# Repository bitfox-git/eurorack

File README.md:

Bitfox Eurorack Modules
=======================

Code License: MIT License

Hardware License: CC-BY-SA 3.0

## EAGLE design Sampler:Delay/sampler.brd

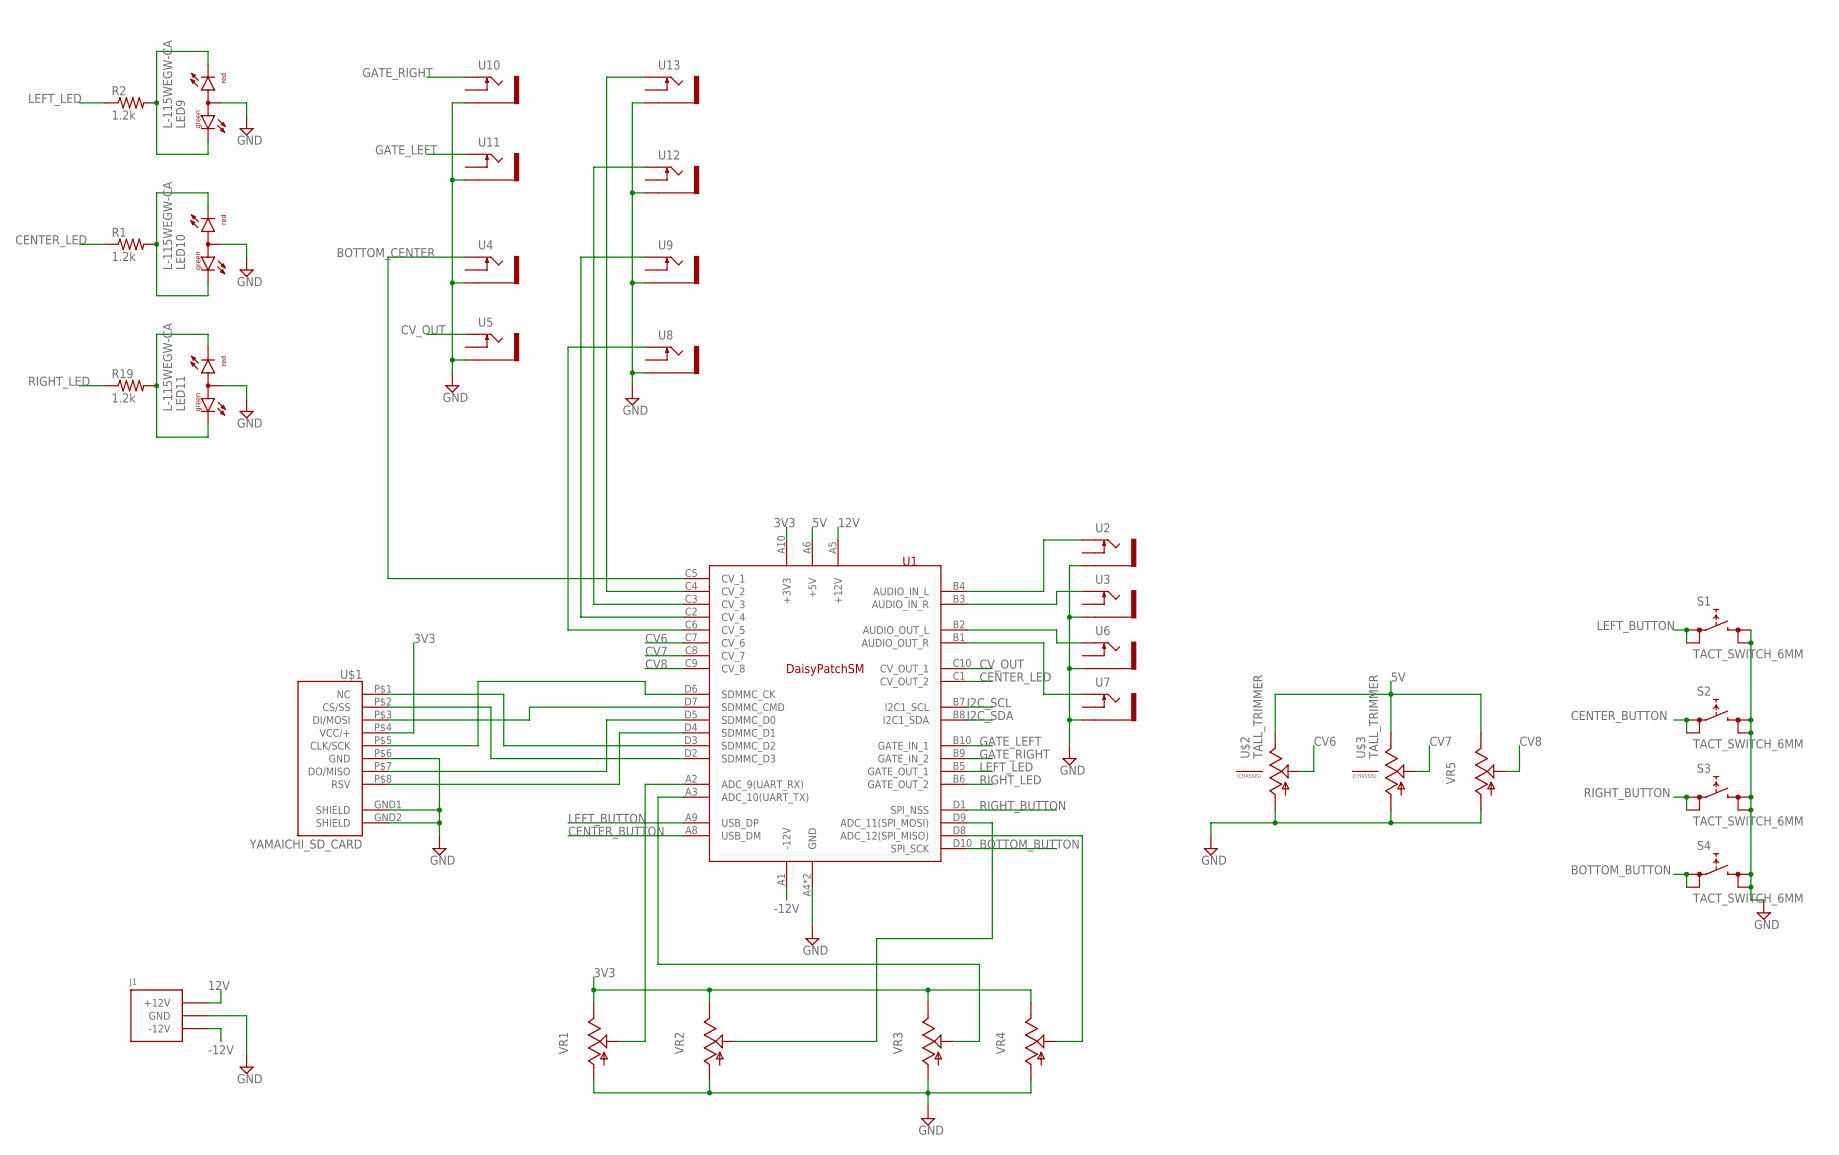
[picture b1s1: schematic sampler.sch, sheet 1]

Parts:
J1: POWER_SIMPLE10; POWER_10
LED9, LED10, LED11: L-115WEGW-CA; DUOLED-A-3MM
R1, R2, R19: 1.2k; R0603
S1, S2, S3, S4: TACT_SWITCH_6MM
U1: ES_DAISY_PATCH_SM; ES_DAISY_PATCH_SM_REV1
U2, U3, U4, U5, U6, U7, U8, U9, U10, U11, U12, U13: THONKICONNNEW; WQP-PJ301M-12_JACK
U$1: YAMAICHI_SD_CARD; YAMAICHI_MICROSD_VERTICAL
U$2, U$3: TALL_TRIMMER
VR1, VR2, VR3, VR4, VR5: 9MM_SNAP-IN_POT_; 9MM_SNAP-IN_POT

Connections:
3V3: U1.A10 (+3V3), U$1.P$4 (VCC/+), VR1.3 (E), VR2.3 (E), VR3.3 (E), VR4.3 (E); also elsewhere on the board
5V: U1.A6 (+5V), U$2.3 (E), U$3.3 (E), VR5.3 (E)
12V: J1.9 (+12V), J1.10 (+12V), U1.A5 (+12V)
-12V: J1.1 (-12V), J1.2 (-12V), U1.A1 (-12V)
BOTTOM_BUTTON: S4.P$1 (1), S4.P$2 (2), U1.D10 (SPI_SCK)
BOTTOM_CENTER: U1.C5 (CV_1), U4.P$1_TIP (TIP)
CENTER_BUTTON: S2.P$1 (1), S2.P$2 (2), U1.A8 (USB_DM)
CENTER_LED: R1.1, U1.C1 (CV_OUT_2)
CV6: U1.C7 (CV_6), U$2.2 (S)
CV7: U1.C8 (CV_7), U$3.2 (S)
CV8: U1.C9 (CV_8), VR5.2 (S)
CV_OUT: U1.C10 (CV_OUT_1), U5.P$1_TIP (TIP)
GATE_LEFT: U1.B10 (GATE_IN_1), U11.P$1_TIP (TIP)
GATE_RIGHT: U1.B9 (GATE_IN_2), U10.P$1_TIP (TIP)
GND: J1.3 (GND), J1.4 (GND), J1.5 (GND), J1.6 (GND), J1.7 (GND), J1.8 (GND), LED9.2 (A), LED10.2 (A), LED11.2 (A), S1.P$3 (3), S1.P$4 (4), S2.P$3 (3), S2.P$4 (4), S3.P$3 (3), S3.P$4 (4), S4.P$3 (3), S4.P$4 (4), U1.A4 (GND), U1.A7 (GND), U2.P$3_SLEEVE (SLEEVE), U3.P$3_SLEEVE (SLEEVE), U4.P$3_SLEEVE (SLEEVE), U5.P$3_SLEEVE (SLEEVE), U6.P$3_SLEEVE (SLEEVE), U7.P$3_SLEEVE (SLEEVE), U8.P$3_SLEEVE (SLEEVE), U9.P$3_SLEEVE (SLEEVE), U10.P$3_SLEEVE (SLEEVE), U11.P$3_SLEEVE (SLEEVE), U12.P$3_SLEEVE (SLEEVE), U13.P$3_SLEEVE (SLEEVE), U$1.GND1 (SHIELD), U$1.GND2 (SHIELD), U$1.P$6 (GND), U$2.1 (A), U$3.1 (A), VR1.1 (A), VR2.1 (A), VR3.1 (A), VR4.1 (A), VR5.1 (A); also elsewhere on the board
I2C_SCL: U1.B7 (I2C1_SCL); also elsewhere on the board
I2C_SDA: U1.B8 (I2C1_SDA); also elsewhere on the board
LEFT_BUTTON: S1.P$1 (1), S1.P$2 (2), U1.A9 (USB_DP)
LEFT_LED: R2.1, U1.B5 (GATE_OUT_1)
unnamed: U1.D3 (SDMMC_D2), U$1.P$1 (NC)
unnamed: LED9.1 (CG), LED9.3 (CR), R2.2
unnamed: U1.D4 (SDMMC_D1), U$1.P$8 (RSV)
unnamed: U1.D5 (SDMMC_D0), U$1.P$7 (DO/MISO)
unnamed: U1.D2 (SDMMC_D3), U$1.P$2 (CS/SS)
unnamed: U1.D6 (SDMMC_CK), U$1.P$5 (CLK/SCK)
unnamed: U1.D7 (SDMMC_CMD), U$1.P$3 (DI/MOSI)
unnamed: U1.B2 (AUDIO_OUT_L), U6.P$1_TIP (TIP)
unnamed: U1.B4 (AUDIO_IN_L), U2.P$1_TIP (TIP)
unnamed: U1.B3 (AUDIO_IN_R), U3.P$1_TIP (TIP)
unnamed: U1.B1 (AUDIO_OUT_R), U7.P$1_TIP (TIP)
unnamed: U1.A3 (ADC_10(UART_TX)), VR3.2 (S)
unnamed: U1.A2 (ADC_9(UART_RX)), VR1.2 (S)
unnamed: U1.D9 (ADC_11(SPI_MOSI)), VR2.2 (S)
unnamed: U1.D8 (ADC_12(SPI_MISO)), VR4.2 (S)
unnamed: LED10.1 (CG), LED10.3 (CR), R1.2
unnamed: U1.C4 (CV_2), U13.P$1_TIP (TIP)
unnamed: U1.C3 (CV_3), U12.P$1_TIP (TIP)
unnamed: LED11.1 (CG), LED11.3 (CR), R19.2
unnamed: U1.C2 (CV_4), U9.P$1_TIP (TIP)
unnamed: U1.C6 (CV_5), U8.P$1_TIP (TIP)
RIGHT_BUTTON: S3.P$1 (1), S3.P$2 (2), U1.D1 (SPI_NSS)
RIGHT_LED: R19.1, U1.B6 (GATE_OUT_2)

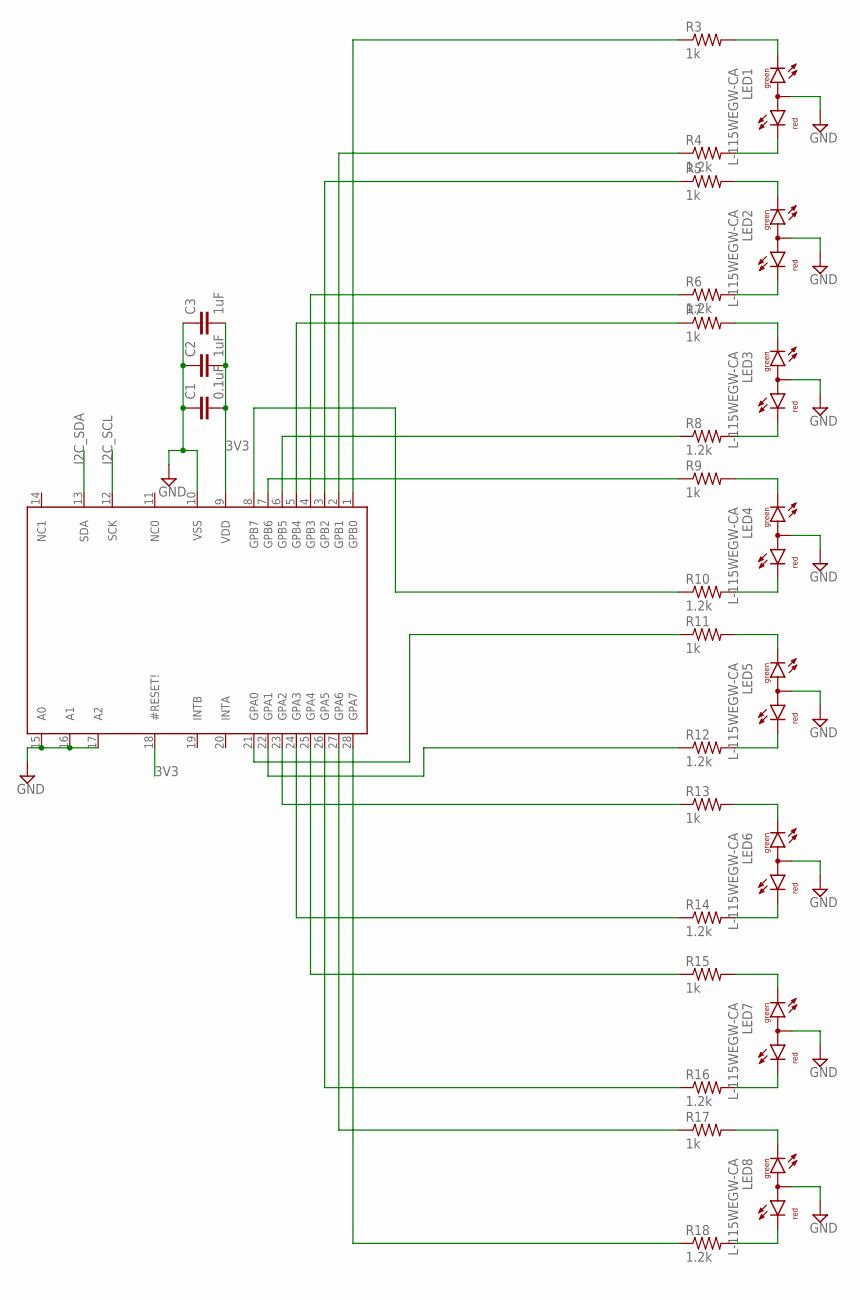
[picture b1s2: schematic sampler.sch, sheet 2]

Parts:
C1: 0.1uF; C0805
C2, C3: 1uF; C0805
LED1, LED2, LED3, LED4, LED5, LED6, LED7, LED8: L-115WEGW-CA; DUOLED-A-3MM
R3, R5, R7, R9, R11, R13, R15, R17: 1k; R0603
R4, R6, R8, R10, R12, R14, R16, R18: 1.2k; R0603
U$4: MCP23017; SSOP28

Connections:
3V3: C1.2, C2.2, C3.2, U$4.9 (VDD), U$4.18 (#RESET!); also elsewhere on the board
GND: C1.1, C2.1, C3.1, LED1.2 (A), LED2.2 (A), LED3.2 (A), LED4.2 (A), LED5.2 (A), LED6.2 (A), LED7.2 (A), LED8.2 (A), U$4.10 (VSS), U$4.15 (A0), U$4.16 (A1), U$4.17 (A2); also elsewhere on the board
I2C_SCL: U$4.12 (SCK); also elsewhere on the board
I2C_SDA: U$4.13 (SDA); also elsewhere on the board
unnamed: R3.1, U$4.1 (GPB0)
unnamed: LED1.1 (CG), R3.2
unnamed: LED1.3 (CR), R4.2
unnamed: R4.1, U$4.2 (GPB1)
unnamed: R5.1, U$4.3 (GPB2)
unnamed: LED2.1 (CG), R5.2
unnamed: LED2.3 (CR), R6.2
unnamed: R6.1, U$4.4 (GPB3)
unnamed: R7.1, U$4.5 (GPB4)
unnamed: LED3.1 (CG), R7.2
unnamed: LED3.3 (CR), R8.2
unnamed: R8.1, U$4.6 (GPB5)
unnamed: R9.1, U$4.7 (GPB6)
unnamed: LED4.1 (CG), R9.2
unnamed: LED4.3 (CR), R10.2
unnamed: R10.1, U$4.8 (GPB7)
unnamed: R11.1, U$4.21 (GPA0)
unnamed: LED5.1 (CG), R11.2
unnamed: LED5.3 (CR), R12.2
unnamed: R12.1, U$4.22 (GPA1)
unnamed: R13.1, U$4.23 (GPA2)
unnamed: LED6.1 (CG), R13.2
unnamed: LED6.3 (CR), R14.2
unnamed: R14.1, U$4.24 (GPA3)
unnamed: R15.1, U$4.25 (GPA4)
unnamed: LED7.1 (CG), R15.2
unnamed: LED7.3 (CR), R16.2
unnamed: R16.1, U$4.26 (GPA5)
unnamed: R17.1, U$4.27 (GPA6)
unnamed: LED8.1 (CG), R17.2
unnamed: LED8.3 (CR), R18.2
unnamed: R18.1, U$4.28 (GPA7)

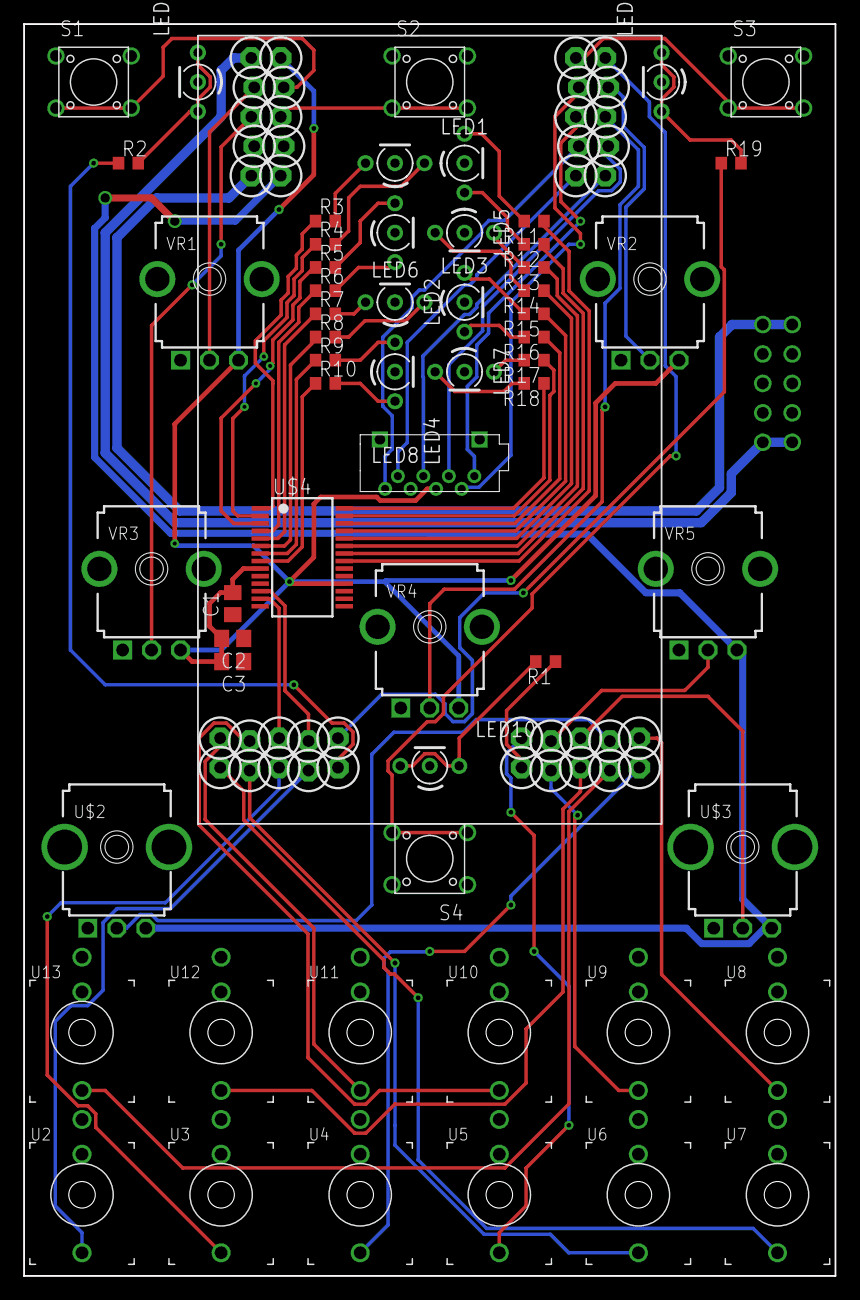
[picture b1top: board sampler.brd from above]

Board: 2 copper layers, 70.0 x 108.0 mm, 60 parts (1 on the bottom side), 74 nets.

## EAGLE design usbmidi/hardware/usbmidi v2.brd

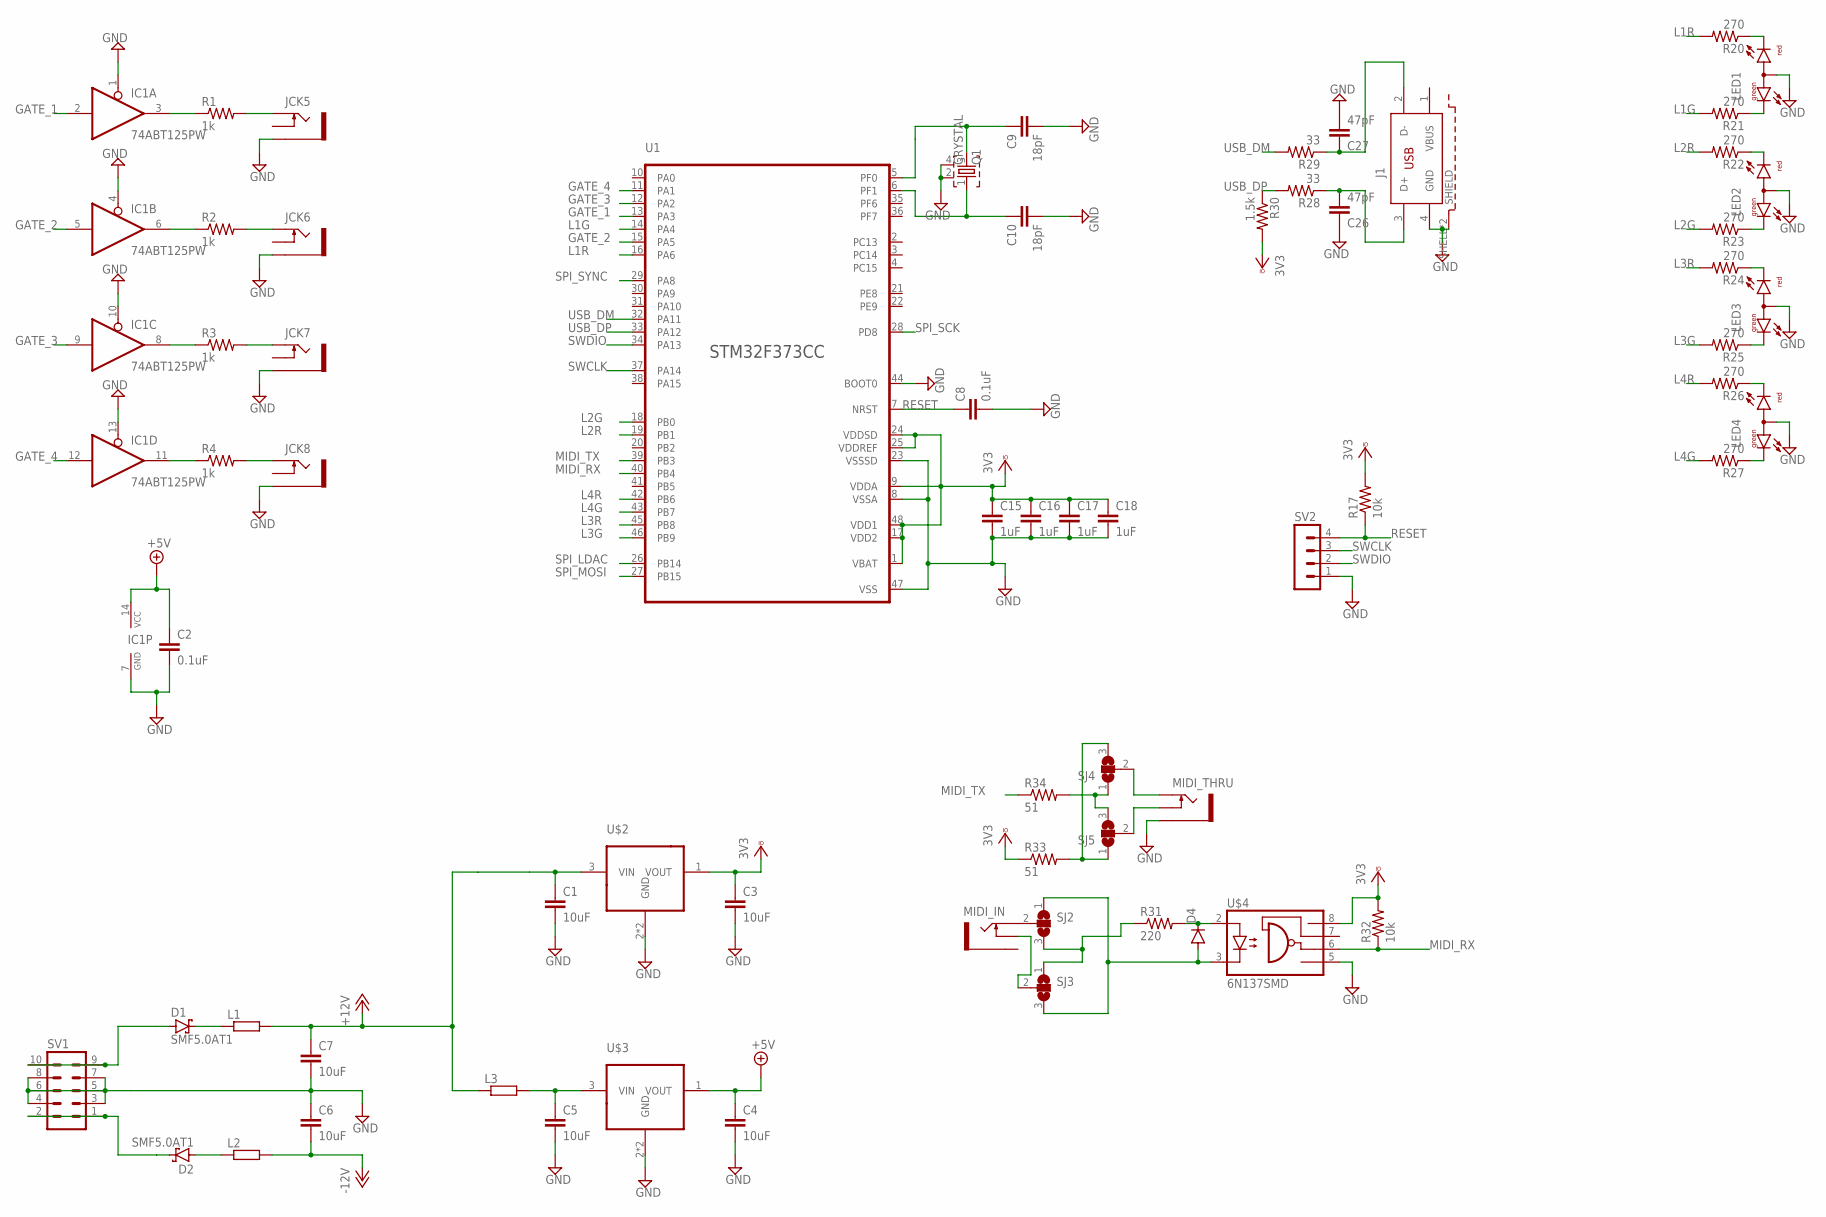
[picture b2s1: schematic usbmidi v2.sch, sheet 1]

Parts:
C1, C3, C4, C5, C6, C7: 10uF; C0805
C2, C8: 0.1uF; C0603K
C9, C10: 18pF; C0603K
C15, C16, C17, C18: 1uF; C0603K
C26, C27: 47pF; C0603K
D1, D2: SMF5.0AT1; SOD123FL
D4: DIODE-SOD123; SOD123
IC1: 74ABT125PW; TSSOP14
J1: 61400413321
JCK5, JCK6, JCK7, JCK8: THONKICONNNEW; WQP-PJ301M-12_JACK
L1, L2, L3: R-EU_R0603; R0603
LED1, LED2, LED3, LED4: L-115WEGW-CA; DUOLED-A-3MM
MIDI_IN: THONKICONNNEW; WQP-PJ301M-12_JACK
MIDI_THRU: THONKICONNNEW; WQP-PJ301M-12_JACK
Q1: CRYSTAL; CTS406
R1, R2, R3, R4: 1k; R0603
R17, R32: 10k; R0603
R20, R21, R22, R23, R24, R25, R26, R27: 270; R0603
R28, R29: 33; R0603
R30: 1.5k; R0603
R31: 220; R0603
R33, R34: 51; R0603
SJ2, SJ3, SJ4, SJ5: SJ2W; SJ_2
SV1: MA05-2
SV2: MA04-1
U1: STM32F373LQFP48; LQFP48
U$2, U$3: LD2981ABUSOT89; SOT89
U$4: 6N137SMD; DIL8-SMD

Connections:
+5V: C2.1, C4.1, IC1.14 (VCC), U$3.1 (VOUT); also elsewhere on the board
+12V: C1.1, C7.1, L1.2, L3.1, U$2.3 (VIN); also elsewhere on the board
-12V: C6.2, L2.2; also elsewhere on the board
GATE_1: IC1.2 (I), U1.13 (PA3)
GATE_2: IC1.5 (I), U1.15 (PA5)
GATE_3: IC1.9 (I), U1.12 (PA2)
GATE_4: IC1.12 (I), U1.11 (PA1)
GND: C1.2, C2.2, C3.2, C4.2, C5.2, C6.1, C7.2, C8.2, C9.2, C10.2, C15.2, C16.2, C17.2, C18.2, C26.1, C27.2, IC1.1 (OE), IC1.4 (OE), IC1.7 (GND), IC1.10 (OE), IC1.13 (OE), J1.4 (GND), J1.SHELL (SHIELD), J1.SHELL1 (SHIELD), JCK5.P$3_SLEEVE (SLEEVE), JCK6.P$3_SLEEVE (SLEEVE), JCK7.P$3_SLEEVE (SLEEVE), JCK8.P$3_SLEEVE (SLEEVE), LED1.2 (A), LED2.2 (A), LED3.2 (A), LED4.2 (A), MIDI_THRU.P$3_SLEEVE (SLEEVE), Q1.2, Q1.4, SV1.3, SV1.4, SV1.5, SV1.6, SV1.7, SV1.8, SV2.1, U1.8 (VSSA), U1.23 (VSSSD), U1.44 (BOOT0), U1.47 (VSS), U$2.2 (GND), U$2.2@1 (GND), U$3.2 (GND), U$3.2@1 (GND), U$4.5 (GND); also elsewhere on the board
L1G: R21.2, U1.14 (PA4)
L1R: R20.2, U1.16 (PA6)
L2G: R23.2, U1.18 (PB0)
L2R: R22.2, U1.19 (PB1)
L3G: R25.2, U1.46 (PB9)
L3R: R24.2, U1.45 (PB8)
L4G: R27.2, U1.43 (PB7)
L4R: R26.2, U1.42 (PB6)
MIDI_RX: R32.1, U1.40 (PB4), U$4.6 (VO)
MIDI_TX: R34.1, U1.39 (PB3)
unnamed: C9.1, Q1.3, U1.5 (PF0)
unnamed: C26.2, J1.3 (D+), R28.1
unnamed: C5.1, L3.2, U$3.3 (VIN)
unnamed: C27.1, J1.2 (D-), R29.1
unnamed: IC1.3 (O), R1.1
unnamed: IC1.6 (O), R2.1
unnamed: IC1.8 (O), R3.1
unnamed: IC1.11 (O), R4.1
unnamed: JCK5.P$1_TIP (TIP), R1.2
unnamed: JCK6.P$1_TIP (TIP), R2.2
unnamed: JCK7.P$1_TIP (TIP), R3.2
unnamed: JCK8.P$1_TIP (TIP), R4.2
unnamed: D4.A, SJ2.1, SJ3.3, U$4.3 (C)
unnamed: D1.C, L1.1
unnamed: D2.A, L2.1
unnamed: D2.C, SV1.1, SV1.2
unnamed: D1.A, SV1.9, SV1.10
unnamed: LED2.1 (CG), R23.1
unnamed: LED2.3 (CR), R22.1
unnamed: LED1.1 (CG), R21.1
unnamed: R31.1, SJ2.3, SJ3.1
unnamed: D4.C, R31.2, U$4.2 (A)
unnamed: MIDI_IN.P$1_TIP (TIP), SJ2.2
unnamed: LED1.3 (CR), R20.1
unnamed: LED4.3 (CR), R26.1
unnamed: LED4.1 (CG), R27.1
unnamed: LED3.1 (CG), R25.1
unnamed: MIDI_IN.P$2_SWITCH (SWITCH), SJ3.2
unnamed: LED3.3 (CR), R24.1
unnamed: C10.1, Q1.1, U1.6 (PF1)
unnamed: MIDI_THRU.P$2_SWITCH (SWITCH), SJ5.2
unnamed: MIDI_THRU.P$1_TIP (TIP), SJ4.2
unnamed: R34.2, SJ4.1, SJ5.3
unnamed: R33.2, SJ4.3, SJ5.1
RESET: C8.1, R17.1, SV2.4, U1.7 (NRST)
SPI_LDAC: U1.26 (PB14); also elsewhere on the board
SPI_MOSI: U1.27 (PB15); also elsewhere on the board
SPI_SCK: U1.28 (PD8); also elsewhere on the board
SPI_SYNC: U1.29 (PA8); also elsewhere on the board
SWCLK: SV2.3, U1.37 (PA14)
SWDIO: SV2.2, U1.34 (PA13)
USB_DM: R29.2, U1.32 (PA11)
USB_DP: R28.2, R30.1, U1.33 (PA12)
VCCIO: C3.1, C15.1, C16.1, C17.1, C18.1, R17.2, R30.2, R32.2, R33.1, U1.1 (VBAT), U1.9 (VDDA), U1.17 (VDD2), U1.24 (VDDSD), U1.25 (VDDREF), U1.48 (VDD1), U$2.1 (VOUT), U$4.8 (VCC); also elsewhere on the board

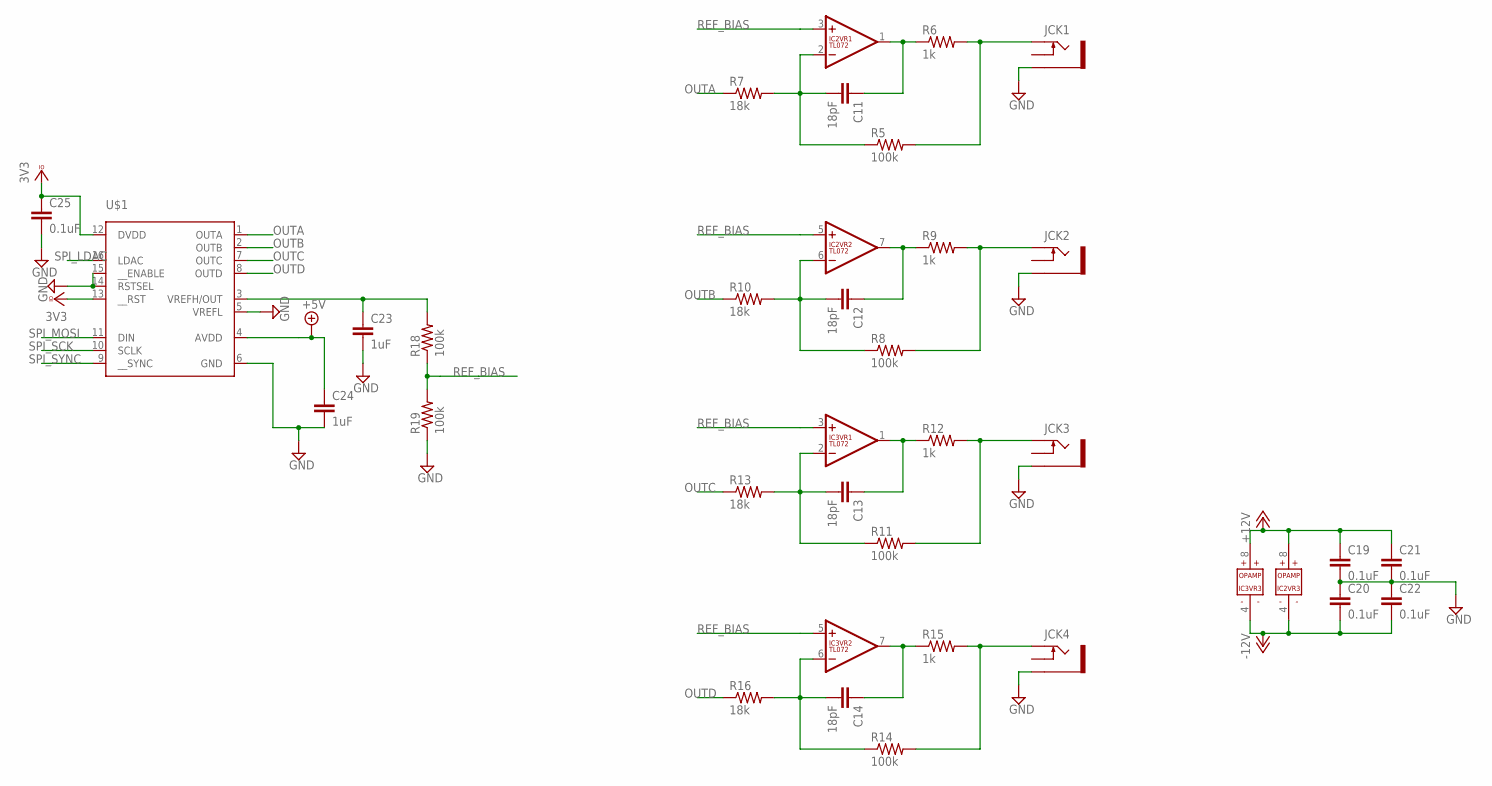
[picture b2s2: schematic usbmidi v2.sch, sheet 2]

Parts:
C11, C12, C13, C14: 18pF; C0603K
C19, C20, C21, C22, C25: 0.1uF; C0603K
C23, C24: 1uF; C0603K
IC2, IC3: TL072; SO08
JCK1, JCK2, JCK3, JCK4: THONKICONNNEW; WQP-PJ301M-12_JACK
R5, R8, R11, R14, R18, R19: 100k; R0603
R6, R9, R12, R15: 1k; R0603
R7, R10, R13, R16: 18k; R0603
U$1: DAC8565; TSSOP16

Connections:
+5V: C24.1, U$1.4 (AVDD); also elsewhere on the board
+12V: C19.1, C21.1, IC2.8 (V+), IC3.8 (V+); also elsewhere on the board
-12V: C20.2, C22.2, IC2.4 (V-), IC3.4 (V-); also elsewhere on the board
GND: C19.2, C20.1, C21.2, C22.1, C23.2, C24.2, C25.2, JCK1.P$3_SLEEVE (SLEEVE), JCK2.P$3_SLEEVE (SLEEVE), JCK3.P$3_SLEEVE (SLEEVE), JCK4.P$3_SLEEVE (SLEEVE), R19.1, U$1.5 (VREFL), U$1.6 (GND), U$1.14 (RSTSEL), U$1.15 (__ENABLE); also elsewhere on the board
unnamed: C11.2, IC2.2 (-IN), R5.1, R7.2
unnamed: C11.1, IC2.1 (OUT), R6.1
unnamed: JCK1.P$1_TIP (TIP), R5.2, R6.2
unnamed: C12.2, IC2.6 (-IN), R8.1, R10.2
unnamed: C12.1, IC2.7 (OUT), R9.1
unnamed: JCK2.P$1_TIP (TIP), R8.2, R9.2
unnamed: C23.1, R18.2, U$1.3 (VREFH/OUT)
unnamed: C13.2, IC3.2 (-IN), R11.1, R13.2
unnamed: C13.1, IC3.1 (OUT), R12.1
unnamed: JCK3.P$1_TIP (TIP), R11.2, R12.2
unnamed: C14.2, IC3.6 (-IN), R14.1, R16.2
unnamed: C14.1, IC3.7 (OUT), R15.1
unnamed: JCK4.P$1_TIP (TIP), R14.2, R15.2
OUTA: R7.1, U$1.1 (OUTA)
OUTB: R10.1, U$1.2 (OUTB)
OUTC: R13.1, U$1.7 (OUTC)
OUTD: R16.1, U$1.8 (OUTD)
REF_BIAS: IC2.3 (+IN), IC2.5 (+IN), IC3.3 (+IN), IC3.5 (+IN), R18.1, R19.2
SPI_LDAC: U$1.16 (LDAC); also elsewhere on the board
SPI_MOSI: U$1.11 (DIN); also elsewhere on the board
SPI_SCK: U$1.10 (SCLK); also elsewhere on the board
SPI_SYNC: U$1.9 (__SYNC); also elsewhere on the board
VCCIO: C25.1, U$1.12 (DVDD), U$1.13 (__RST); also elsewhere on the board

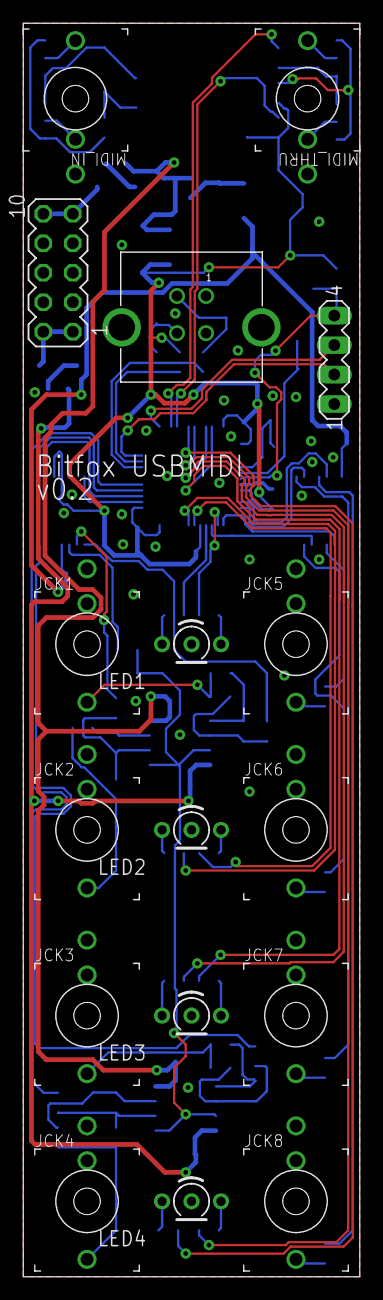
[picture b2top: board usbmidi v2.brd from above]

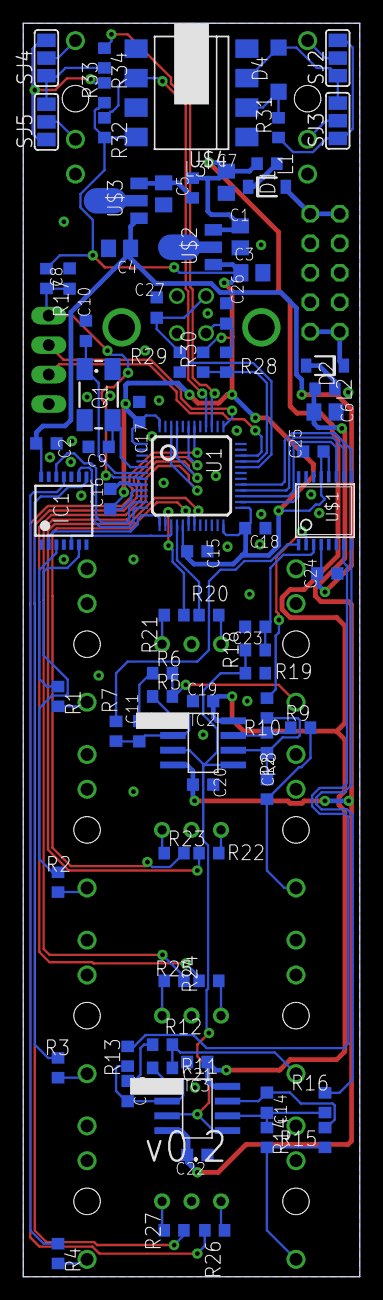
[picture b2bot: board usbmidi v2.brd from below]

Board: 2 copper layers, 29.0 x 108.0 mm, 97 parts (80 on the bottom side), 80 nets.

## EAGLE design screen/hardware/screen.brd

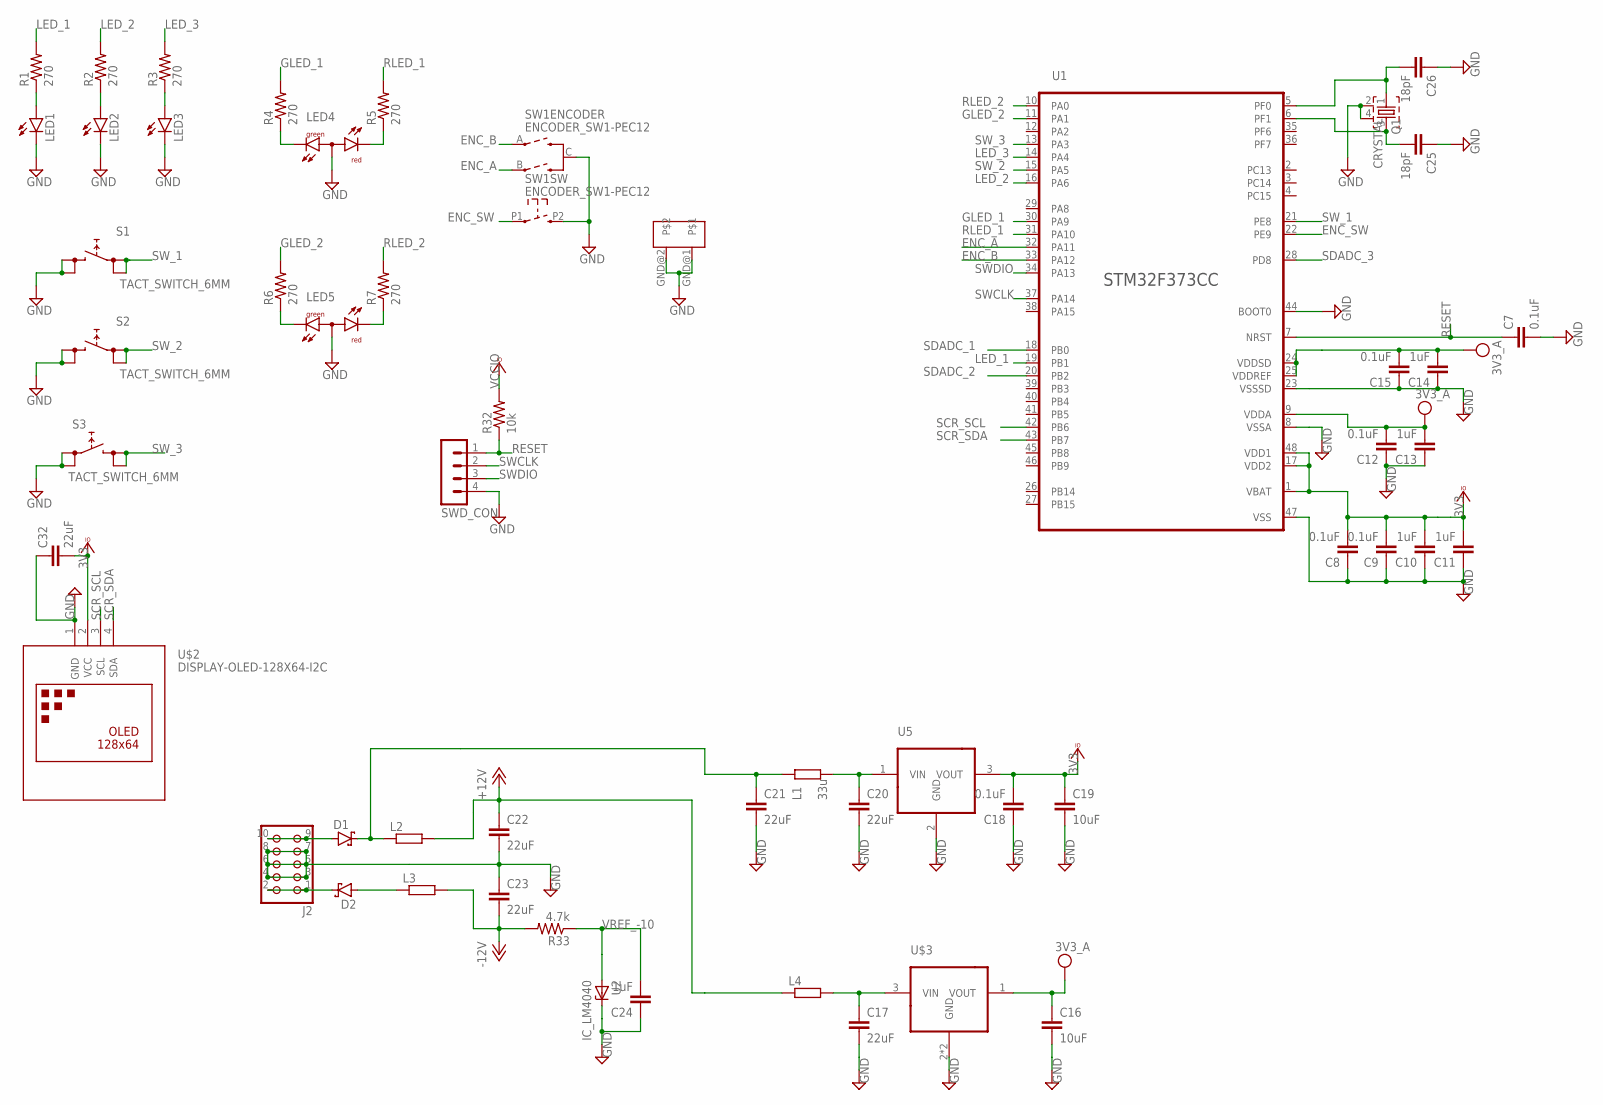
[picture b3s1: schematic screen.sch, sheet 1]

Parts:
C7, C8, C9, C12, C15, C18: 0.1uF; C0603
C10, C11, C13, C14, C24: 1uF; C0603
C16, C19: 10uF; C1206
C17, C20, C21, C22, C23, C32: 22uF; C1206
C25, C26: 18pF; C0603
D1, D2: SMF5.0AT1; SOD123FL
J2: CON_HEADER_2X05-PTH+SHROUDED_A; PINSHRD_PTH_2X05
L1: 33u; R0805
L2, L3, L4: R-EU_R0603; R0603
LED1, LED2, LED3: LED3MM
LED4, LED5: L-115WEGW-CA; DUOLED-A-3MM
Q1: CRYSTAL; CTS406
R1, R2, R3, R4, R5, R6, R7: 270; R0603
R32: 10k; R0603
R33: 4.7k; R0603
S1, S2, S3: TACT_SWITCH_6MM
SW1: ENCODER_SW1-PEC12; PEC12_INCREMENTAL_ENCODER
SWD_CON: MA04-1
U1: STM32F373LQFP48; LQFP48
U2: IC_LM4040; SOT-23
U5: R-78E-0.5; TO-220_RECOM
U$2: DISPLAY-OLED-128X64-I2C
U$3: LD2981ABUSOT89; SOT89

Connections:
+12V: C22.1, L2.2, L4.1; also elsewhere on the board
-12V: C23.2, L3.2, R33.2; also elsewhere on the board
ENC_A: SW1.B, U1.32 (PA11)
ENC_B: SW1.A, U1.33 (PA12)
ENC_SW: SW1.P1 (1), U1.22 (PE9)
GLED_1: R4.2, U1.30 (PA9)
GLED_2: R6.2, U1.11 (PA1)
GND: C7.2, C8.1, C9.1, C10.1, C11.1, C12.1, C13.1, C14.1, C15.1, C16.2, C17.2, C18.1, C19.2, C20.2, C21.2, C22.2, C23.1, C24.1, C25.1, C26.1, C32.1, J2.3, J2.4, J2.5, J2.6, J2.7, J2.8, LED1.K (C), LED2.K (C), LED3.K (C), LED4.2 (A), LED5.2 (A), Q1.2, Q1.4, S1.P$3 (3), S1.P$4 (4), S2.P$3 (3), S2.P$4 (4), S3.P$1 (1), S3.P$2 (2), SW1.C, SW1.GND@1, SW1.GND@2, SW1.P2 (2), SWD_CON.4, U1.8 (VSSA), U1.23 (VSSSD), U1.44 (BOOT0), U1.47 (VSS), U2.1 (C), U5.2 (GND), U$2.1 (GND), U$3.2 (GND), U$3.2@1 (GND); also elsewhere on the board
LED_1: R1.2, U1.19 (PB1)
LED_2: R2.2, U1.16 (PA6)
LED_3: R3.2, U1.14 (PA4)
unnamed: LED1.A, R1.1
unnamed: LED2.A, R2.1
unnamed: LED3.A, R3.1
unnamed: LED4.1 (CG), R4.1
unnamed: LED4.3 (CR), R5.1
unnamed: C25.2, Q1.3, U1.6 (PF1)
unnamed: D2.C, J2.1, J2.2
unnamed: LED5.1 (CG), R6.1
unnamed: LED5.3 (CR), R7.1
unnamed: D1.A, J2.9, J2.10
unnamed: C21.1, D1.C, L1.1, L2.1
unnamed: C26.2, Q1.1, U1.5 (PF0)
unnamed: C20.1, L1.2, U5.1 (VIN)
unnamed: C17.1, L4.2, U$3.3 (VIN)
unnamed: D2.A, L3.1
RESET: C7.1, R32.1, SWD_CON.1, U1.7 (NRST)
RLED_1: R5.2, U1.31 (PA10)
RLED_2: R7.2, U1.10 (PA0)
SCR_SCL: U1.42 (PB6), U$2.3 (SCL)
SCR_SDA: U1.43 (PB7), U$2.4 (SDA)
SDADC_1: U1.18 (PB0); also elsewhere on the board
SDADC_2: U1.20 (PB2); also elsewhere on the board
SDADC_3: U1.28 (PD8); also elsewhere on the board
SWCLK: SWD_CON.2, U1.37 (PA14)
SWDIO: SWD_CON.3, U1.34 (PA13)
SW_1: S1.P$1 (1), S1.P$2 (2), U1.21 (PE8)
SW_2: S2.P$1 (1), S2.P$2 (2), U1.15 (PA5)
SW_3: S3.P$3 (3), S3.P$4 (4), U1.13 (PA3)
VCC: C12.2, C13.2, C14.2, C15.2, C16.1, U1.9 (VDDA), U1.24 (VDDSD), U1.25 (VDDREF), U$3.1 (VOUT); also elsewhere on the board
VCCIO: C8.2, C9.2, C10.2, C11.2, C18.2, C19.1, C32.2, R32.2, U1.1 (VBAT), U1.17 (VDD2), U1.48 (VDD1), U5.3 (VOUT), U$2.2 (VCC)
VREF_-10: C24.2, R33.1, U2.2 (A), U2.3 (A); also elsewhere on the board

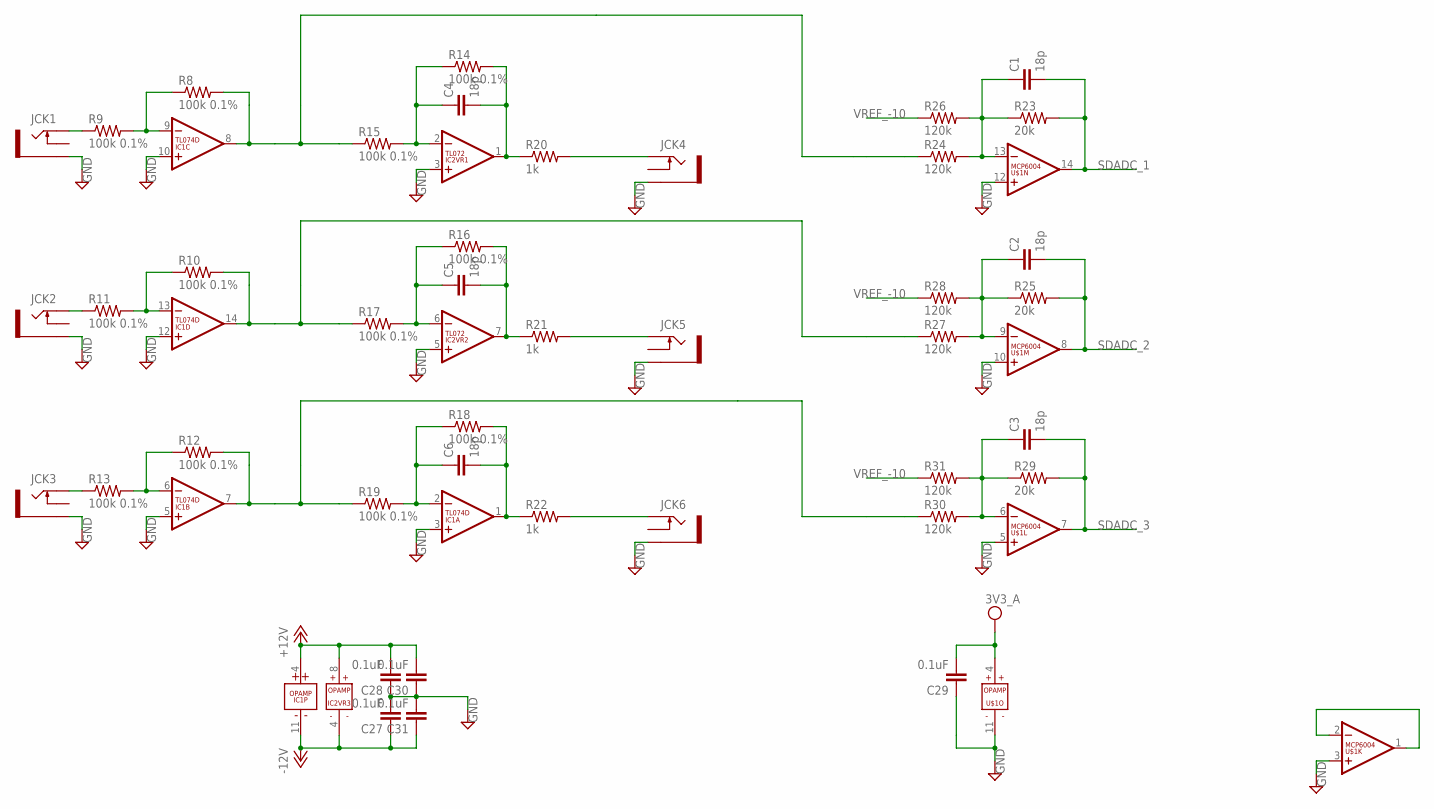
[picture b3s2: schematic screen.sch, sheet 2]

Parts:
C1, C2, C3, C4, C5, C6: 18p; C0603
C27, C28, C29, C30, C31: 0.1uF; C0603
IC1: TL074D; SO14
IC2: TL072; SO08
JCK1, JCK2, JCK3, JCK4, JCK5, JCK6: THONKICONNNEW; WQP-PJ301M-12_JACK
R8, R9, R10, R11, R12, R13, R14, R15, R16, R17, R18, R19: 100k 0.1%; R0603
R20, R21, R22: 1k; R0603
R23, R25, R29: 20k; R0603
R24, R26, R27, R28, R30, R31: 120k; R0603
U$1: MCP6004; SO14

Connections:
+12V: C28.2, C30.2, IC1.4 (V+), IC2.8 (V+); also elsewhere on the board
-12V: C27.1, C31.1, IC1.11 (V-), IC2.4 (V-); also elsewhere on the board
GND: C27.2, C28.1, C29.1, C30.1, C31.2, IC1.3 (+IN), IC1.5 (+IN), IC1.10 (+IN), IC1.12 (+IN), IC2.3 (+IN), IC2.5 (+IN), JCK1.P$3_SLEEVE (SLEEVE), JCK2.P$3_SLEEVE (SLEEVE), JCK3.P$3_SLEEVE (SLEEVE), JCK4.P$3_SLEEVE (SLEEVE), JCK5.P$3_SLEEVE (SLEEVE), JCK6.P$3_SLEEVE (SLEEVE), U$1.3 (+IN), U$1.5 (+IN), U$1.10 (+IN), U$1.11 (V-), U$1.12 (+IN); also elsewhere on the board
unnamed: IC1.9 (-IN), R8.1, R9.2
unnamed: IC1.13 (-IN), R10.1, R11.2
unnamed: C6.2, IC1.1 (OUT), R18.2, R22.1
unnamed: C1.1, R23.1, R24.2, R26.2, U$1.13 (-IN)
unnamed: JCK1.P$1_TIP (TIP), R9.1
unnamed: JCK2.P$1_TIP (TIP), R11.1
unnamed: IC1.6 (-IN), R12.1, R13.2
unnamed: C4.2, IC2.1 (OUT), R14.2, R20.1
unnamed: JCK3.P$1_TIP (TIP), R13.1
unnamed: C4.1, IC2.2 (-IN), R14.1, R15.2
unnamed: U$1.1 (OUT), U$1.2 (-IN)
unnamed: C5.2, IC2.7 (OUT), R16.2, R21.1
unnamed: C5.1, IC2.6 (-IN), R16.1, R17.2
unnamed: C2.1, R25.1, R27.2, R28.2, U$1.9 (-IN)
unnamed: C6.1, IC1.2 (-IN), R18.1, R19.2
unnamed: C3.1, R29.1, R30.2, R31.2, U$1.6 (-IN)
unnamed: JCK5.P$1_TIP (TIP), R21.2
unnamed: JCK4.P$1_TIP (TIP), R20.2
unnamed: JCK6.P$1_TIP (TIP), R22.2
SDADC_1: C1.2, R23.2, U$1.14 (OUT); also elsewhere on the board
SDADC_2: C2.2, R25.2, U$1.8 (OUT); also elsewhere on the board
SDADC_3: C3.2, R29.2, U$1.7 (OUT); also elsewhere on the board
SIGNAL_1: IC1.8 (OUT), R8.2, R15.1, R24.1
SIGNAL_2: IC1.14 (OUT), R10.2, R17.1, R27.1
SIGNAL_3: IC1.7 (OUT), R12.2, R19.1, R30.1
VCC: C29.2, U$1.4 (V+); also elsewhere on the board
VREF_-10: R26.1, R28.1, R31.1; also elsewhere on the board

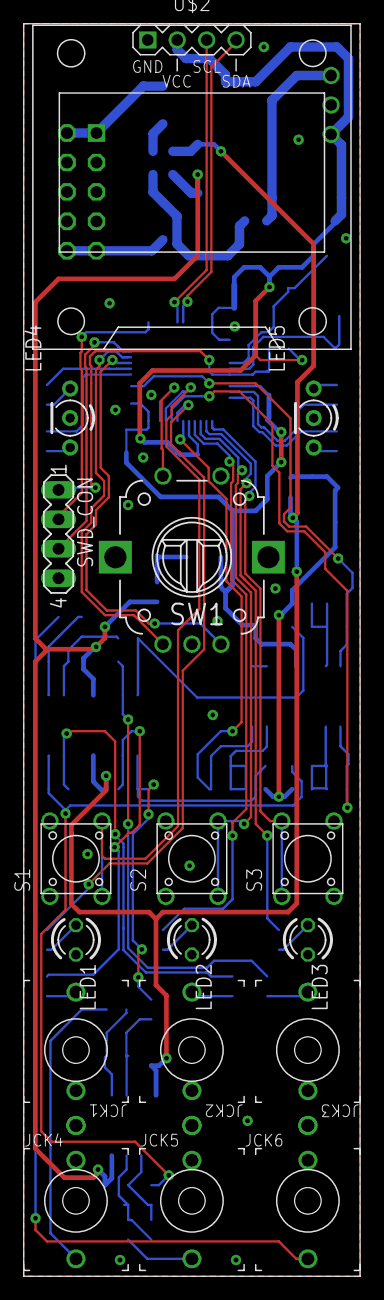
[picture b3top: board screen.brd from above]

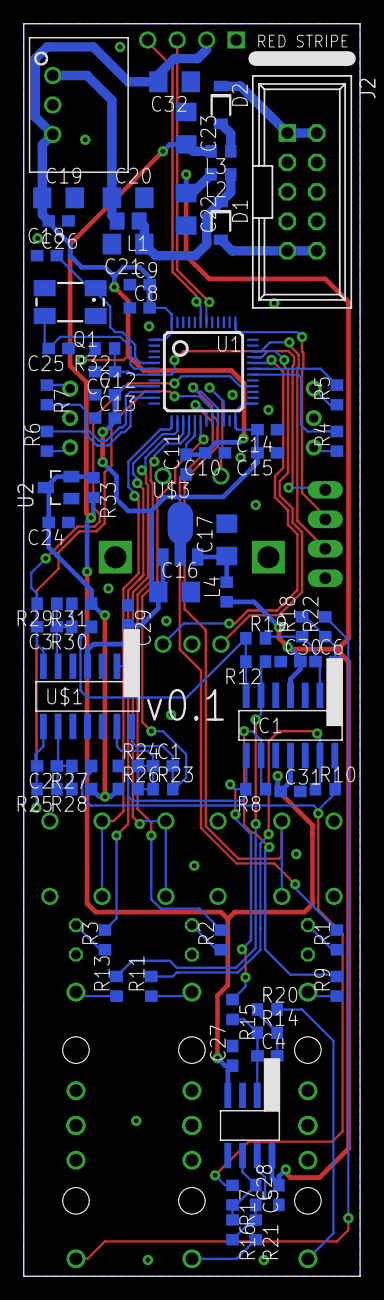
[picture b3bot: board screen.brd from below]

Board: 2 copper layers, 29.0 x 108.0 mm, 97 parts (80 on the bottom side), 64 nets.

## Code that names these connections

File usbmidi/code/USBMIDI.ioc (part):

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Mcu.Name=STM32F373C(8-B-C)Tx
Mcu.Package=LQFP48
Mcu.UserName=STM32F373CCTx
PA1.Signal=GPIO_Output
PA11.Mode=Device
PA11.Signal=USB_DM
PA12.GPIOParameters=GPIO_PuPd
PA12.GPIO_PuPd=GPIO_NOPULL
PA12.Mode=Device
PA12.Signal=USB_DP
PA13.Mode=Serial_Wire
PA13.Signal=SYS_JTMS-SWDIO
PA14.Mode=Serial_Wire
PA14.Signal=SYS_JTCK-SWCLK
PA2.Signal=GPIO_Output
PA3.Signal=GPIO_Output
PA4.Signal=S_TIM3_CH2
PA5.Signal=GPIO_Output
PA6.Signal=S_TIM3_CH1
PA8.GPIOParameters=GPIO_Speed
PA8.GPIO_Speed=GPIO_SPEED_FREQ_HIGH
PA8.Signal=GPIO_Output
PB0.Signal=S_TIM3_CH3
PB1.Signal=S_TIM3_CH4
PB14.Signal=GPIO_Output
PB15.Mode=TX_Only_Simplex_Unidirect_Master
PB15.Signal=SPI2_MOSI
PB3.Mode=Asynchronous
PB3.Signal=USART2_TX
PB4.Mode=Asynchronous
PB4.Signal=USART2_RX
PB6.Signal=S_TIM4_CH1
PB7.Signal=S_TIM4_CH2
PB8.Signal=S_TIM4_CH3
PB9.Signal=S_TIM4_CH4
PD8.Mode=TX_Only_Simplex_Unidirect_Master
PD8.Signal=SPI2_SCK
PF0-OSC_IN.Mode=HSE-External-Oscillator
PF0-OSC_IN.Signal=RCC_OSC_IN
PF1-OSC_OUT.Mode=HSE-External-Oscillator
PF1-OSC_OUT.Signal=RCC_OSC_OUT
RCC.HSEPLLFreq_Value=8000000
RCC.HSE_VALUE=8000000
RCC.SYSCLKFreq_VALUE=72000000
RCC.SYSCLKSource=RCC_SYSCLKSOURCE_PLLCLK
board=custom

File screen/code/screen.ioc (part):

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Mcu.Name=STM32F373C(8-B-C)Tx
Mcu.Package=LQFP48
Mcu.UserName=STM32F373CCTx
PA0.Signal=S_TIM2_CH1_ETR
PA1.Signal=S_TIM2_CH2
PA10.Signal=S_TIM2_CH4
PA11.GPIOParameters=GPIO_PuPd
PA11.GPIO_PuPd=GPIO_PULLUP
PA11.Signal=S_TIM4_CH1
PA12.GPIOParameters=GPIO_PuPd
PA12.GPIO_PuPd=GPIO_PULLUP
PA12.Signal=S_TIM4_CH2
PA13.Mode=Serial_Wire
PA13.Signal=SYS_JTMS-SWDIO
PA14.Mode=Serial_Wire
PA14.Signal=SYS_JTCK-SWCLK
PA3.GPIOParameters=GPIO_PuPd
PA3.GPIO_PuPd=GPIO_PULLUP
PA3.Signal=GPIO_Input
PA4.Signal=S_TIM3_CH2
PA5.GPIOParameters=GPIO_PuPd
PA5.GPIO_PuPd=GPIO_PULLUP
PA5.Signal=GPIO_Input
PA6.Signal=S_TIM3_CH1
PA9.Signal=S_TIM2_CH3
PB0.Mode=IN6-Single-Ended zero reference
PB0.Signal=SDADC1_AIN6P
PB1.Signal=S_TIM3_CH4
PB2.Mode=IN6-Single-Ended zero reference
PB2.Signal=SDADC2_AIN6P
PB6.Mode=I2C
PB6.Signal=I2C1_SCL
PB7.Mode=I2C
PB7.Signal=I2C1_SDA
PD8.Mode=IN6-Single-Ended zero reference
PD8.Signal=SDADC3_AIN6P
PE8.GPIOParameters=GPIO_PuPd
PE8.GPIO_PuPd=GPIO_PULLUP
PE8.Signal=GPIO_Input
PE9.GPIOParameters=GPIO_PuPd
PE9.GPIO_PuPd=GPIO_PULLUP
PE9.Signal=GPIO_Input
PF0-OSC_IN.Mode=HSE-External-Oscillator
PF0-OSC_IN.Signal=RCC_OSC_IN
PF1-OSC_OUT.Mode=HSE-External-Oscillator
PF1-OSC_OUT.Signal=RCC_OSC_OUT
RCC.HSEPLLFreq_Value=8000000
RCC.HSE_VALUE=8000000
RCC.SYSCLKFreq_VALUE=72000000
RCC.SYSCLKSource=RCC_SYSCLKSOURCE_PLLCLK
board=custom

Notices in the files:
parts and their libraries:
diy-modules: Released under the Creative Commons Attribution 4.0 International License: http://creativecommons.org/licenses/by/4.0
Wurth_Elektronik_Electromechanic_Input-O: Copyright: Würth Elektronik
